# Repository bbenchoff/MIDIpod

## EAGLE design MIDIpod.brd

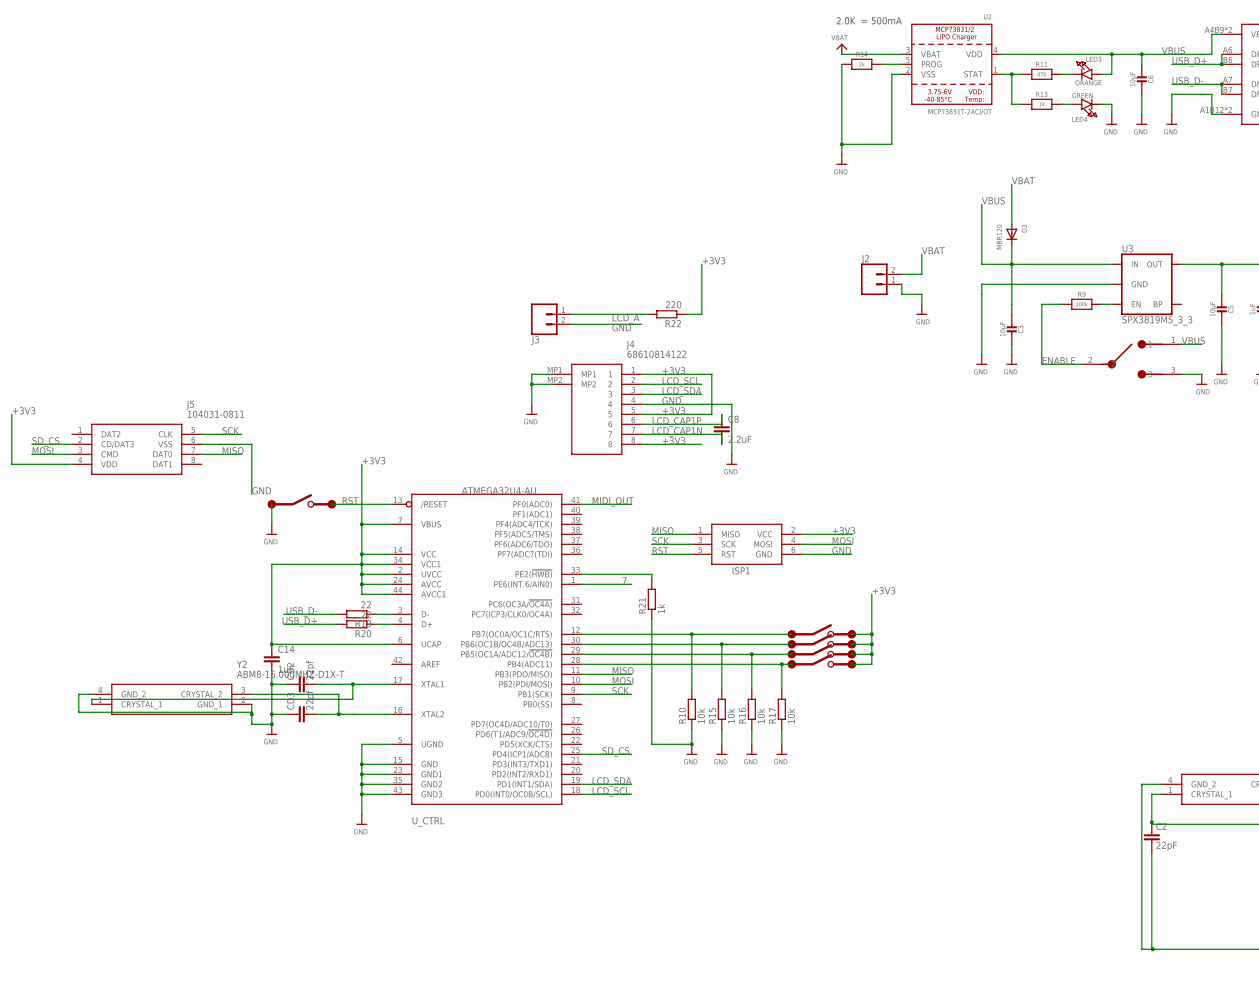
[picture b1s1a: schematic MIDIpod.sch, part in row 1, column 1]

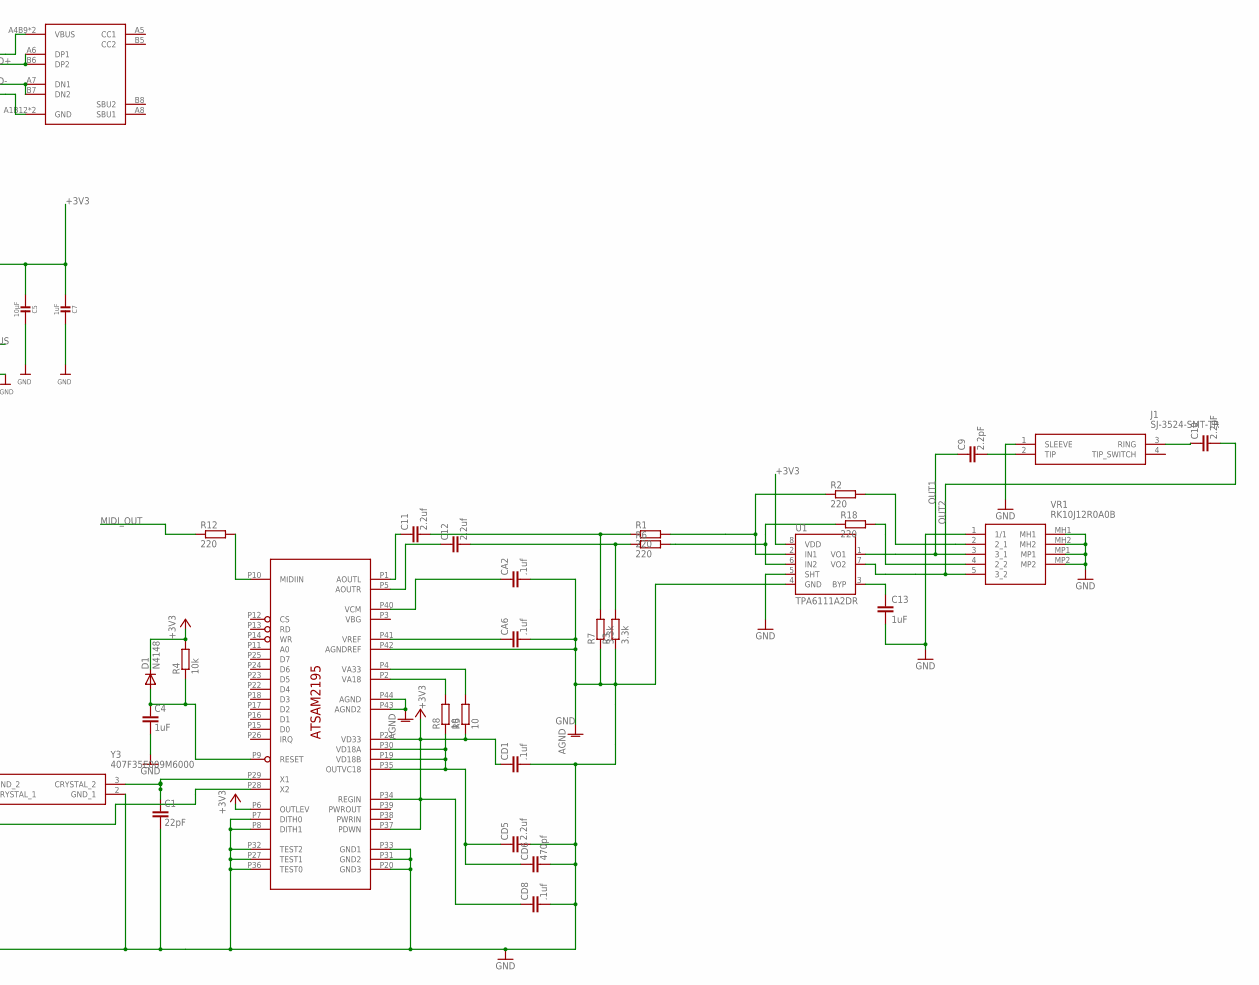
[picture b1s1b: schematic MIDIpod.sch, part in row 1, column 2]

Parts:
BUTTON1, BUTTON2, BUTTON3, BUTTON4, BUTTON5: 1U_PAD; SILICONE_SWITCH
C1, C2: 22pF; C0603
C3, C5, C6: 10µF; 0805-NO
C4: 1uF; C0603
C7: 1uF; 0805-NO
C8: 2.2uF; 0805
C9, C10: 2.2pF; C0603
C11, C12: 2.2uf; C0603
C13, C14: 1uF; 0402
CA2, CA6: .1uf; C0603
CD1, CD8: .1uf; C0603
CD2, CD3: 22pf; C0603
CD5: 2.2uf; C0603
CD6: 470pf; C0603
D1: N4148; SOD-123
D3: MBR120; SOD-123
ISP1: AVRISP-6; AVRISP
J1: SJ-3524-SMT-TR
J2, J3: CONN_02; 1X02
J4: 68610814122
J5: 104031-0811; 1040310811
LED3: ORANGE; CHIPLED_0805_NOOUTLINE
LED4: GREEN; CHIPLED_0805_NOOUTLINE
POWER_SW: ALPSSLIDESW; SWITCH-SSSS810701
R1, R2, R6, R12, R18, R22: 220; R0603
R3, R7: 3.3k; R0603
R4, R10, R15, R16, R17: 10k; R0603
R5, R8: 10; R0603
R9: 100k; 0805-NO
R11: 470; 0805-NO
R13: 1K; 0805-NO
R14: 2k; 0805-NO
R19, R20: 22; R0603
R21: 1k; R0603
U1: TPA6111A2DR; SO08
U2: MCP73831T-2ACI/OT; SOT23-5
U3: SPX3819M5_3_3; SOT23-5
U$1: ATSAM2195
U$43: TYPE-C-31-M-12
U_CTRL: ATMEGA32U4-AU; TQFP44
VR1: RK10J12R0A0B
Y2: ABM8-16.000MHZ-D1X-T; ABM816000MHZD1XT
Y3: 407F35E009M6000

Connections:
7: U_CTRL.1 (PE6(INT.6/AIN0))
+3V3: BUTTON1.P$1, BUTTON2.P$1, BUTTON3.P$1, BUTTON4.P$1, C5.1, C7.1, C14.1, CD1.1, CD8.1, D1.C, ISP1.2 (VCC), J4.1, J4.5, J4.8, J5.4 (VDD), R4.2, R5.1, R22.1, U1.8 (VDD), U3.5 (OUT), U$1.P6 (OUTLEV), U$1.P21 (VD33), U$1.P34 (REGIN), U$1.P37 (PDWN), U_CTRL.2 (UVCC), U_CTRL.6 (UCAP), U_CTRL.7 (VBUS), U_CTRL.14 (VCC), U_CTRL.24 (AVCC), U_CTRL.34 (VCC1), U_CTRL.44 (AVCC1)
CA11: C12.1, U$1.P5 (AOUTR)
ENABLE: POWER_SW.2, R9.2
GND: BUTTON5.P$2, C1.2, C2.2, C3.2, C4.2, C5.2, C6.2, C7.2, C13.2, C14.2, CA2.2, CA6.2, CD1.2, CD2.1, CD3.1, CD5.2, CD6.2, CD8.2, ISP1.6 (GND), J1.1 (SLEEVE), J2.1, J3.2, J4.4, J4.MP1, J4.MP2, J5.6 (VSS), LED4.C, POWER_SW.3, R3.1, R7.1, R10.1, R14.2, R15.1, R16.1, R17.1, R21.1, U1.4 (GND), U1.5 (SHT), U2.2 (VSS), U3.2 (GND), U$1.P7 (DITH0), U$1.P8 (DITH1), U$1.P20 (GND3), U$1.P27 (TEST1), U$1.P31 (GND2), U$1.P32 (TEST2), U$1.P33 (GND1), U$1.P36 (TEST0), U$1.P42 (AGNDREF), U$1.P43 (AGND2), U$1.P44 (AGND), U$43.A1B12 (GND), U$43.B1A12 (GND), U_CTRL.5 (UGND), U_CTRL.15 (GND), U_CTRL.23 (GND1), U_CTRL.35 (GND2), U_CTRL.43 (GND3), VR1.1 (1/1), VR1.MH1, VR1.MH2, VR1.MP1, VR1.MP2, Y2.2 (GND_1), Y2.4 (GND_2), Y3.2 (GND_1), Y3.4 (GND_2)
LCD_A: J3.1, R22.2
LCD_CAP1N: C8.2, J4.7
LCD_CAP1P: C8.1, J4.6
LCD_SCL: J4.2, U_CTRL.18 (PD0(INT0/OC0B/SCL))
LCD_SDA: J4.3, U_CTRL.19 (PD1(INT1/SDA))
MIDI_OUT: R12.1, U_CTRL.41 (PF0(ADC0))
MISO: ISP1.1 (MISO), J5.7 (DAT0), U_CTRL.11 (PB3(PDO/MISO))
MOSI: ISP1.4 (MOSI), J5.3 (CMD), U_CTRL.10 (PB2(PDI/MOSI))
unnamed: C9.2, J1.2 (TIP)
unnamed: R12.2, U$1.P10 (MIDIIN)
unnamed: C2.1, U$1.P28 (X2), Y3.1 (CRYSTAL_1)
unnamed: C4.1, D1.A, R4.1, U$1.P9 (RESET)
unnamed: C1.1, U$1.P29 (X1), Y3.3 (CRYSTAL_2)
unnamed: CD5.1, CD6.1, R8.1, U$1.P19 (VD18B), U$1.P30 (VD18A), U$1.P35 (OUTVC18)
unnamed: R8.2, U$1.P2 (VA18)
unnamed: C11.1, U$1.P1 (AOUTL)
unnamed: LED3.C, R11.1
unnamed: C11.2, R1.1, R7.2
unnamed: C12.2, R3.2, R6.1
unnamed: CA2.1, U$1.P40 (VCM)
unnamed: R5.2, U$1.P4 (VA33)
unnamed: R1.2, R2.1, U1.2 (IN1)
unnamed: R11.2, R13.2, U2.1 (STAT)
unnamed: R6.2, R18.1, U1.6 (IN2)
unnamed: R14.1, U2.5 (PROG)
unnamed: LED4.A, R13.1
unnamed: R9.1, U3.3 (EN)
unnamed: CA6.1, U$1.P41 (VREF)
unnamed: BUTTON1.P$2, R10.2, U_CTRL.12 (PB7(OC0A/OC1C/RTS))
unnamed: BUTTON2.P$2, R15.2, U_CTRL.30 (PB6(OC1B/OC4B/ADC13))
unnamed: BUTTON3.P$2, R16.2, U_CTRL.29 (PB5(OC1A/ADC12/!OC4B))
unnamed: BUTTON4.P$2, R17.2, U_CTRL.28 (PB4(ADC11))
unnamed: C10.1, J1.3 (RING)
unnamed: R2.2, VR1.2 (2_1)
unnamed: C13.1, U1.3 (BYP)
unnamed: R19.1, U_CTRL.3 (D-)
unnamed: R18.2, VR1.4 (2_2)
unnamed: R20.1, U_CTRL.4 (D+)
unnamed: R21.2, U_CTRL.33 (PE2(!HWB))
unnamed: CD2.2, U_CTRL.17 (XTAL1), Y2.1 (CRYSTAL_1)
unnamed: CD3.2, U_CTRL.16 (XTAL2), Y2.3 (CRYSTAL_2)
OUT1: C9.1, U1.1 (VO1), VR1.3 (3_1)
OUT2: C10.2, U1.7 (VO2), VR1.5 (3_2)
RST: BUTTON5.P$1, ISP1.5 (RST), U_CTRL.13 (/RESET)
SCK: ISP1.3 (SCK), J5.5 (CLK), U_CTRL.9 (PB1(SCK))
SD_CS: J5.2 (CD/DAT3), U_CTRL.25 (PD4(ICP1/ADC8))
USB_D+: R20.2, U$43.A6 (DP1), U$43.B6 (DP2)
USB_D-: R19.2, U$43.A7 (DN1), U$43.B7 (DN2)
VBAT: D3.A, J2.2, U2.3 (VBAT)
VBUS: C3.1, C6.1, D3.C, LED3.A, POWER_SW.1, U2.4 (VDD), U3.1 (IN), U$43.A4B9 (VBUS), U$43.B4A9 (VBUS)

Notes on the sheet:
2.0K = 500mA

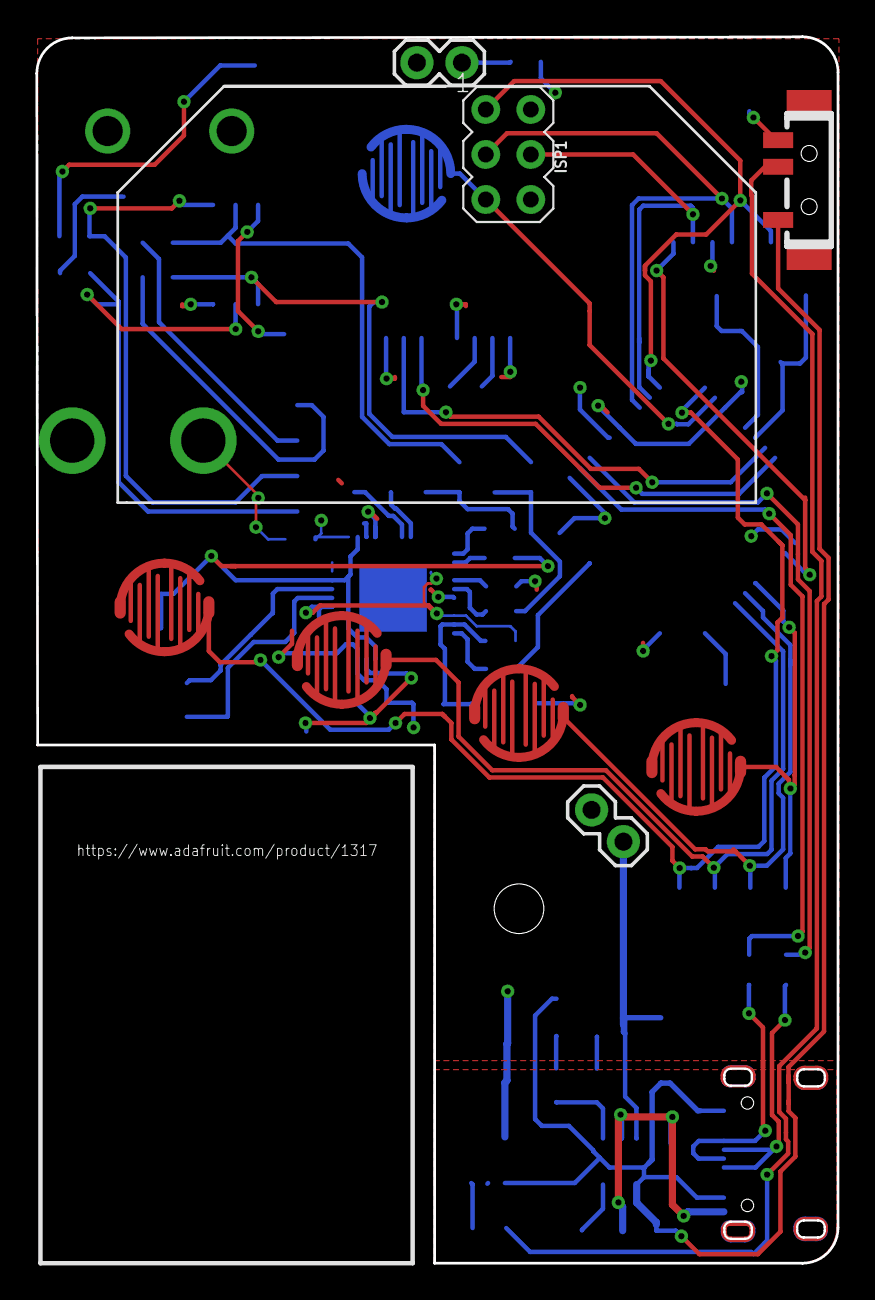
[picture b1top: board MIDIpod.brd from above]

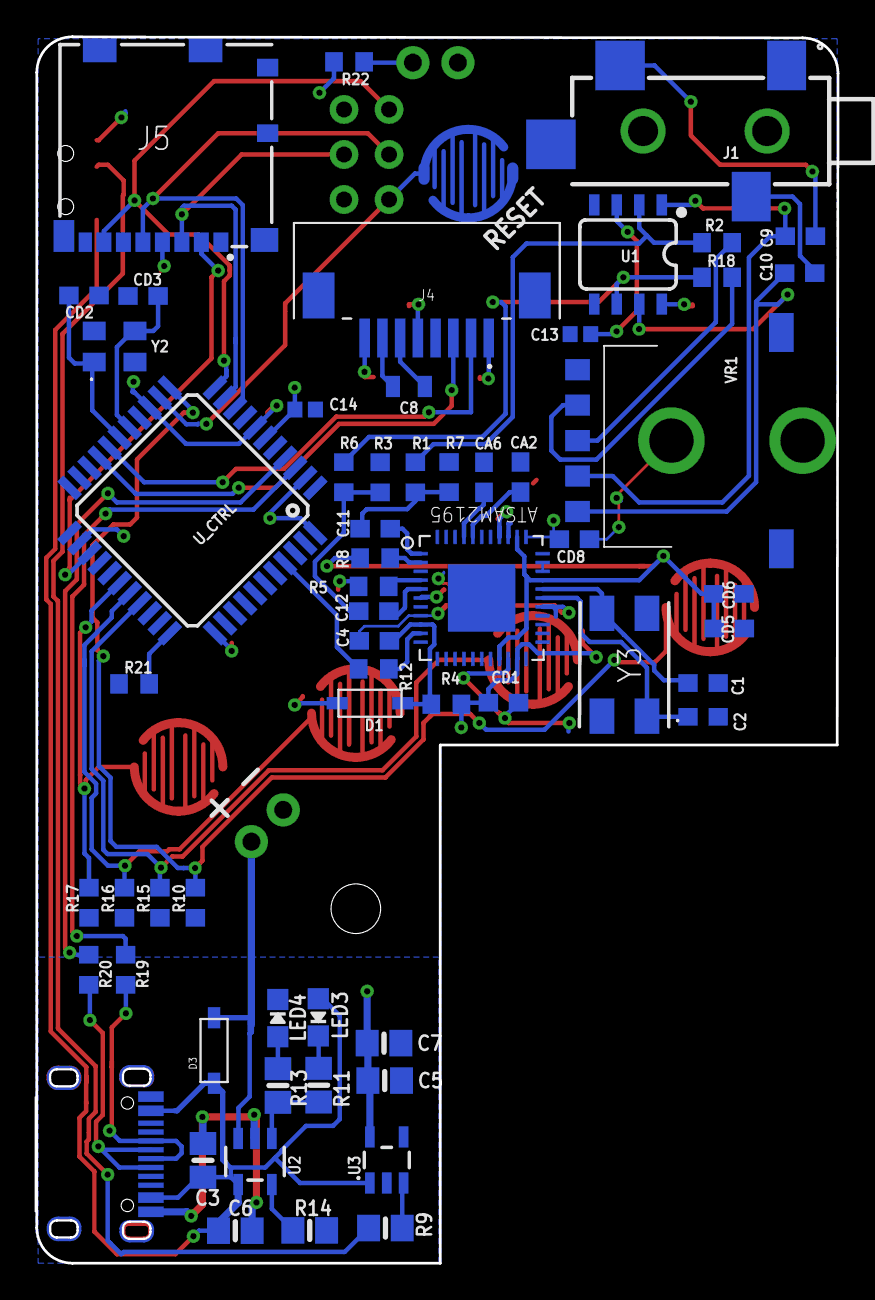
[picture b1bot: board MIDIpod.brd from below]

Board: 2 copper layers, 45.2 x 69.2 mm, 69 parts (61 on the bottom side), 54 nets.

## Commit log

2021-09-20 something something schematic
2021-09-24 updated, sent to oshpark
2021-09-27 made the midipod I can build

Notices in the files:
parts and their libraries:
microbuilder: This work is placed in the public domain, and may be freely used for commercial and non-commercial work with the following conditions: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
SparkFun-Connectors: Licensing: Creative Commons ShareAlike 4.0 International - https://creativecommons.org/licenses/by-sa/4.0
